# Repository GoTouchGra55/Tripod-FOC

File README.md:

# Tripod (FOC)

A device that works as the brushless FOC motor driver of a tri-legged hopping robot!

## Overview

Tripod-FOC is a 4 layer printed circuit board which is to be used as the field-oriented control based motor driver of a major robot project I've been working on.

The board handles the robot's main motor control providing the necessary measurement for its brushless motors.

## Design

### Routes

### Schematics

SEE [SCHEMATICS](KiCAD/FOC.pdf)

## Build Instructions

1. Order the PCB using the provided [files](KiCAD/production).
2. Solder all SMD components according to the schematic and PCB layout.
3. Inspect all solder joints and check for shorts.
4. Connect the peripherals according to the schematic.
5. Flash the firmware and verify all interfaces.
6. Test the power rails before connecting the motors.

## BOM

| Category           | Item             |    Quantity | Supplier     | Unit Cost (USD) | Total Cost (USD) | Notes                               |
| ------------------ | ---------------- | ----------: | ------------ | --------------: | ---------------: | ----------------------------------- |
| PCB manufacturing  | JLCPCB order     |           1 | JLCPCB       |         $427.16 |          $427.16 | JLCPCB order subtotal               |
| Shipping           | FedEx shipping   |           1 | FedEx        |          $36.62 |           $36.62 | Included in the quoted JLCPCB total |
| Passive components | SMD resistors    | As required | Daraz        |           $0.00 |            $0.00 | Already owned                       |
| Passive components | SMD capacitors   | As required | Daraz        |           $0.00 |            $0.00 | Already owned                       |
| Passive components | Circular magnets |      1 pack | Amazon India |           $2.65 |            $2.65 | Ordered from amazon.in              |
| **TOTAL**          |                  |             |              |                 |      **$466.43** |                                     |

### SEE [BOM](BOM.csv)

## IMPORTANT

1. Use a 3-4s LiPo battery if you decide to use this board in your project. Discard the battery if it smells "funny".

2. Check for any damage on the pcb as it can be the reason for a catastrophic failure.

## License

MIT-License - SEE [LICENSE](LICENSE)

## Author

Shaurya Tamang  
Contact: [Email](shauryatamand.dev@gmail.com)

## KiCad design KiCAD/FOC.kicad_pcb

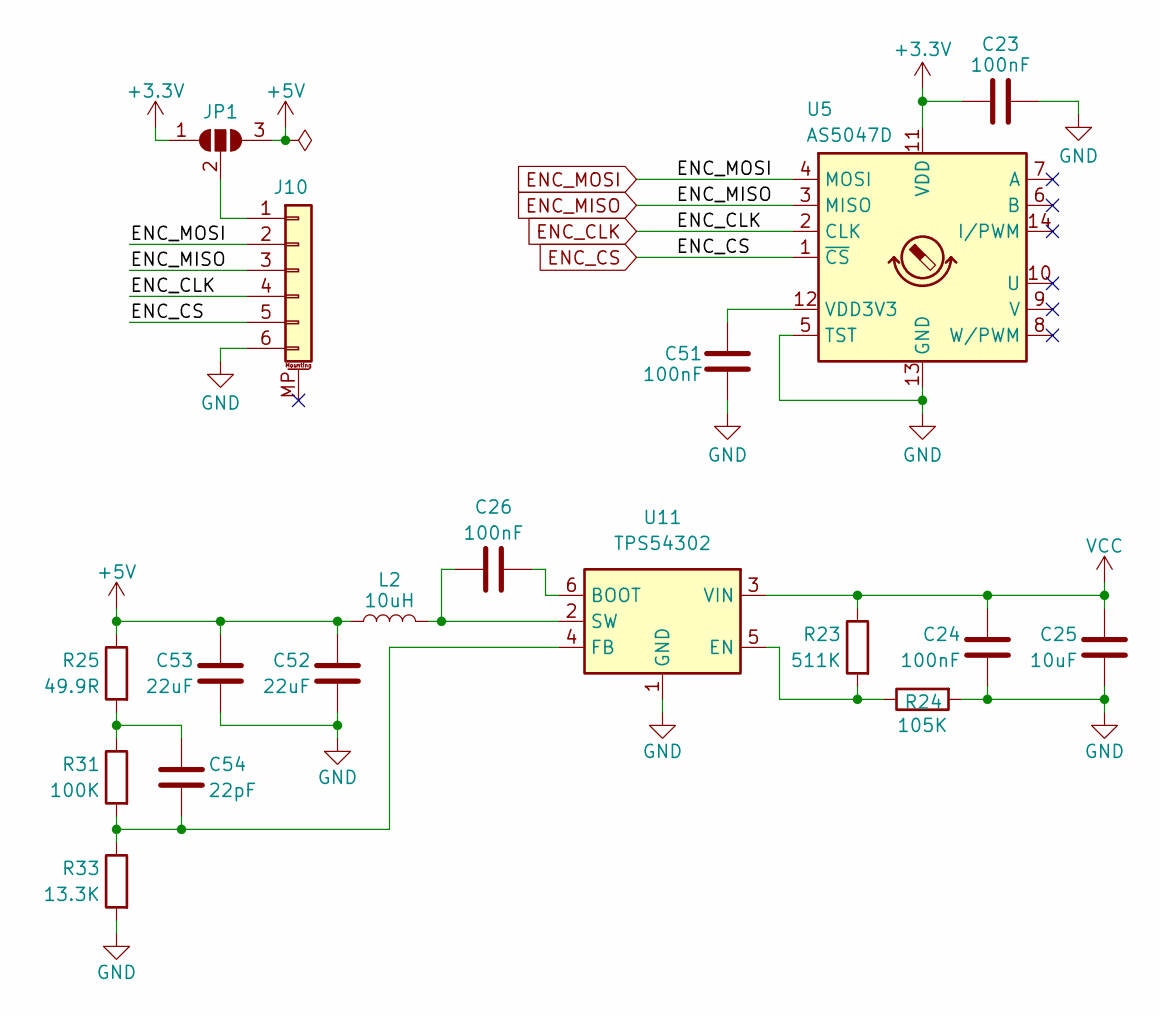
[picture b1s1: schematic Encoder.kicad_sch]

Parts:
C23, C24, C26, C51: 100nF; C_0402_1005Metric
C25: 10uF; C_0603_1608Metric
C52, C53: 22uF; C_0603_1608Metric
C54: 22pF; C_0402_1005Metric
J10: Conn_01x06_MountingPin; JST_SH_SM06B-SRSS-TB_1x06-1MP_P1.00mm_Horizontal
JP1: SolderJumper_3_Open; SolderJumper-3_P1.3mm_Open_Pad1.0x1.5mm_NumberLabels
L2: 10uH; L_Cenker_CKCS3012
R23: 511K; R_0603_1608Metric
R24: 105K; R_0603_1608Metric
R25: 49.9R; R_0402_1005Metric
R31: 100K; R_0603_1608Metric
R33: 13.3K; R_0603_1608Metric
U5: AS5047D; TSSOP-14_4.4x5mm_P0.65mm
U11: TPS54302; SOT-23-6

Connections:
+3.3V: C23.1, JP1.1 (A), U5.11 (VDD); also elsewhere on the board
+5V: C52.1, C53.1, JP1.3 (B), L2.2, R25.1; also elsewhere on the board
ENC_CLK: J10.4, U5.2 (CLK); also elsewhere on the board
ENC_CS: J10.5, U5.1 (~CS); also elsewhere on the board
ENC_MISO: J10.3, U5.3 (MISO); also elsewhere on the board
ENC_MOSI: J10.2, U5.4 (MOSI); also elsewhere on the board
GND: C23.2, C24.2, C25.2, C51.1, C52.2, C53.2, J10.6, R24.2, R33.2, U5.5 (TST), U5.13 (GND), U11.1 (GND); also elsewhere on the board
unnamed: C54.1, R25.2, R31.1
unnamed: J10.1, JP1.2 (C)
unnamed: C51.2, U5.12 (VDD3V3)
unnamed: C26.1, U11.6 (BOOT)
unnamed: R23.2, R24.1, U11.5 (EN)
unnamed: C54.2, R31.2, R33.1, U11.4 (FB)
unnamed: C26.2, L2.1, U11.2 (SW)
VCC: C24.1, C25.1, R23.1, U11.3 (VIN); also elsewhere on the board

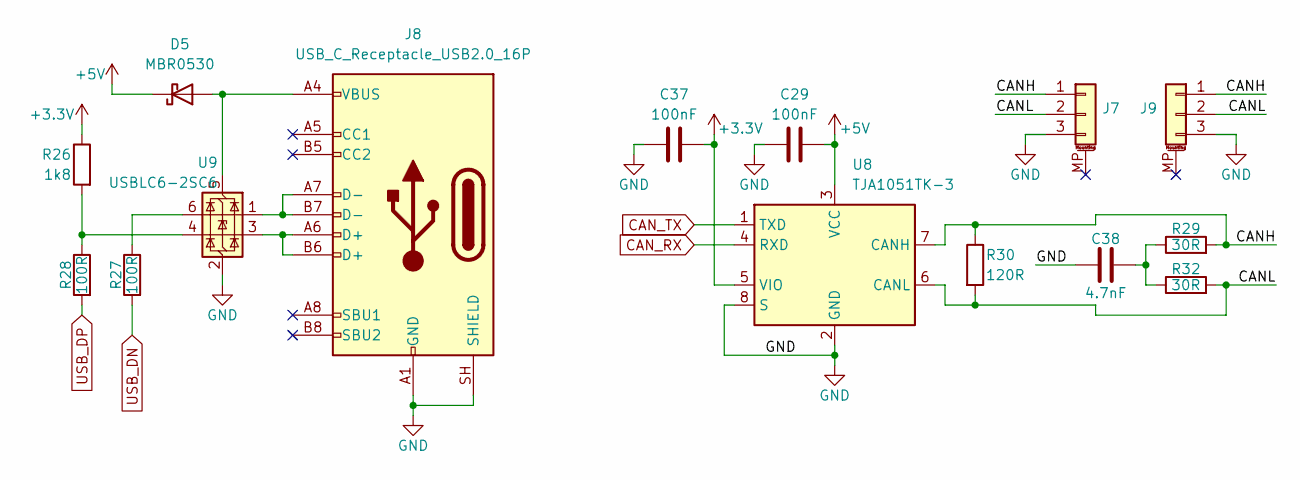
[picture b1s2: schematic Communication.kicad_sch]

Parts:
C29, C37: 100nF; C_0402_1005Metric
C38: 4.7nF; C_0402_1005Metric
D5: MBR0530; D_SOD-123; LCSC Part # C5204746
J7, J9: Conn_01x03_MountingPin; JST_SH_SM03B-SRSS-TB_1x03-1MP_P1.00mm_Horizontal
J8: USB_C_Receptacle_USB2.0_16P; USB_C_Receptacle_GCT_USB4105-xx-A_16P_TopMnt_Horizontal
R26: 1k8; R_0402_1005Metric; LCSC Part # C163481
R27, R28: 100R; R_0402_1005Metric; LCSC Part # C705627
R29, R32: 30R; R_0402_1005Metric; LCSC Part # C852718
R30: 120R; R_0402_1005Metric; LCSC Part # C125925
U8: TJA1051TK-3; HVSON-8-1EP_3x3mm_P0.65mm_EP1.6x2.4mm
U9: USBLC6-2SC6; SOT-23-6; LCSC Part # C2827654

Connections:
+3.3V: C37.2, R26.1, U8.5 (VIO); also elsewhere on the board
+5V: C29.2, D5.1 (K), U8.3 (VCC); also elsewhere on the board
/Communication/CANH: J7.1, J9.1, R29.2, R30.1, U8.7 (CANH)
/Communication/CANL: J7.2, J9.2, R30.2, R32.2, U8.6 (CANL)
CAN_RX: U8.4 (RXD); also elsewhere on the board
CAN_TX: U8.1 (TXD); also elsewhere on the board
GND: C29.1, C37.1, C38.1, J7.3, J8.A1 (GND), J8.A12 (GND), J8.B1 (GND), J8.B12 (GND), J8.SH (SHIELD), J9.3, U8.2 (GND), U8.8 (S), U8.9 (GND), U9.2 (GND); also elsewhere on the board
unnamed: C38.2, R29.1, R32.1
unnamed: D5.2 (A), J8.A4 (VBUS), J8.A9 (VBUS), J8.B4 (VBUS), J8.B9 (VBUS), U9.5 (VBUS)
unnamed: J8.A6 (D+), J8.B6 (D+), U9.3 (I/O2)
unnamed: J8.A7 (D-), J8.B7 (D-), U9.1 (I/O1)
unnamed: R26.2, R28.1, U9.4 (I/O2)
unnamed: R27.1, U9.6 (I/O1)
USB_DN: R27.2; also elsewhere on the board
USB_DP: R28.2; also elsewhere on the board

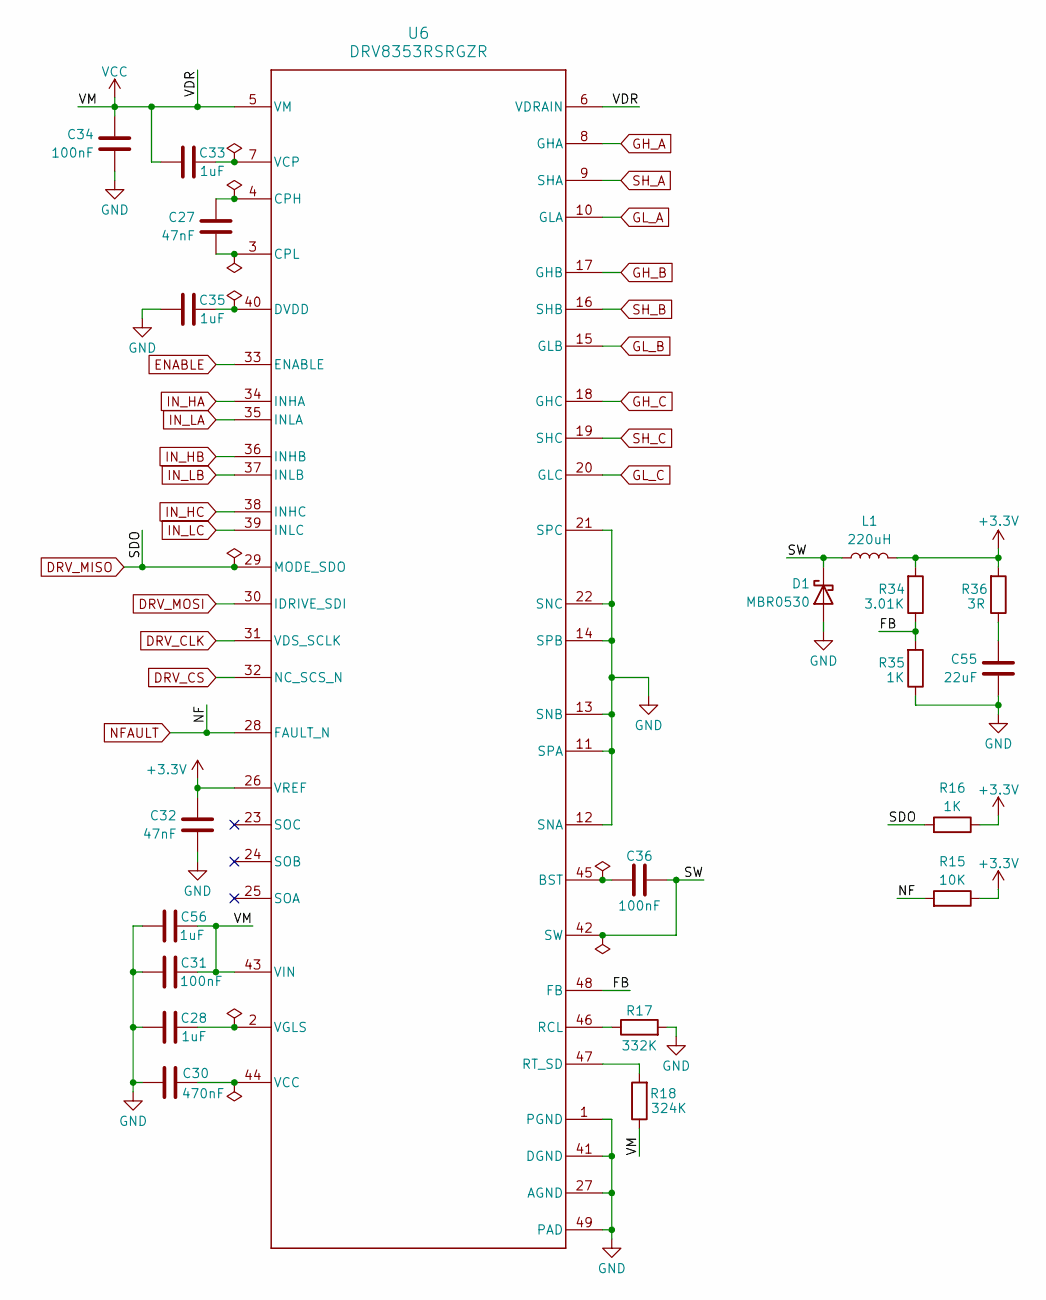
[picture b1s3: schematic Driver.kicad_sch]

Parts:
C27, C32: 47nF; C_0402_1005Metric
C28, C33, C35, C56: 1uF; C_0603_1608Metric
C30: 470nF; C_0402_1005Metric
C31, C34, C36: 100nF; C_0402_1005Metric
C55: 22uF; C_0603_1608Metric
D1: MBR0530; R_0402_1005Metric
L1: 220uH; L_Cenker_CKCS5040
R15: 10K; R_0603_1608Metric
R16, R35: 1K; R_0402_1005Metric
R17: 332K; R_0603_1608Metric
R18: 324K; R_0603_1608Metric
R34: 3.01K; R_0603_1608Metric
R36: 3R; R_0402_1005Metric
U6: DRV8353RSRGZR; RGZ0048L

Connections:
+3.3V: C32.1, L1.1, R15.1, R16.1, R34.2, R36.2, U6.26 (VREF); also elsewhere on the board
/Driver/FB: R34.1, R35.2, U6.48 (FB)
/Driver/SW: C36.1, D1.1 (K), L1.2, U6.42 (SW)
DRV_CLK: U6.31 (VDS_SCLK); also elsewhere on the board
DRV_CS: U6.32 (NC_SCS_N); also elsewhere on the board
DRV_MISO: R16.2, U6.29 (MODE_SDO); also elsewhere on the board
DRV_MOSI: U6.30 (IDRIVE_SDI); also elsewhere on the board
ENABLE: U6.33 (ENABLE); also elsewhere on the board
GH_A: U6.8 (GHA); also elsewhere on the board
GH_B: U6.17 (GHB); also elsewhere on the board
GH_C: U6.18 (GHC); also elsewhere on the board
GL_A: U6.10 (GLA); also elsewhere on the board
GL_B: U6.15 (GLB); also elsewhere on the board
GL_C: U6.20 (GLC); also elsewhere on the board
GND: C28.1, C30.1, C31.1, C32.2, C34.2, C35.1, C55.2, C56.1, D1.2 (A), R17.2, R35.1, U6.1 (PGND), U6.11 (SPA), U6.12 (SNA), U6.13 (SNB), U6.14 (SPB), U6.21 (SPC), U6.22 (SNC), U6.27 (AGND), U6.41 (DGND), U6.49 (PAD); also elsewhere on the board
IN_HA: U6.34 (INHA); also elsewhere on the board
IN_HB: U6.36 (INHB); also elsewhere on the board
IN_HC: U6.38 (INHC); also elsewhere on the board
IN_LA: U6.35 (INLA); also elsewhere on the board
IN_LB: U6.37 (INLB); also elsewhere on the board
IN_LC: U6.39 (INLC); also elsewhere on the board
NFAULT: R15.2, U6.28 (FAULT_N); also elsewhere on the board
unnamed: C55.1, R36.1
unnamed: C36.2, U6.45 (BST)
unnamed: C27.1, U6.4 (CPH)
unnamed: C27.2, U6.3 (CPL)
unnamed: C35.2, U6.40 (DVDD)
unnamed: R17.1, U6.46 (RCL)
unnamed: R18.2, U6.47 (RT_SD)
unnamed: C30.2, U6.44 (VCC)
unnamed: C33.2, U6.7 (VCP)
unnamed: C28.2, U6.2 (VGLS)
SH_A: U6.9 (SHA); also elsewhere on the board
SH_B: U6.16 (SHB); also elsewhere on the board
SH_C: U6.19 (SHC); also elsewhere on the board
VCC: C31.2, C33.1, C34.1, C56.2, R18.1, U6.5 (VM), U6.6 (VDRAIN), U6.43 (VIN); also elsewhere on the board

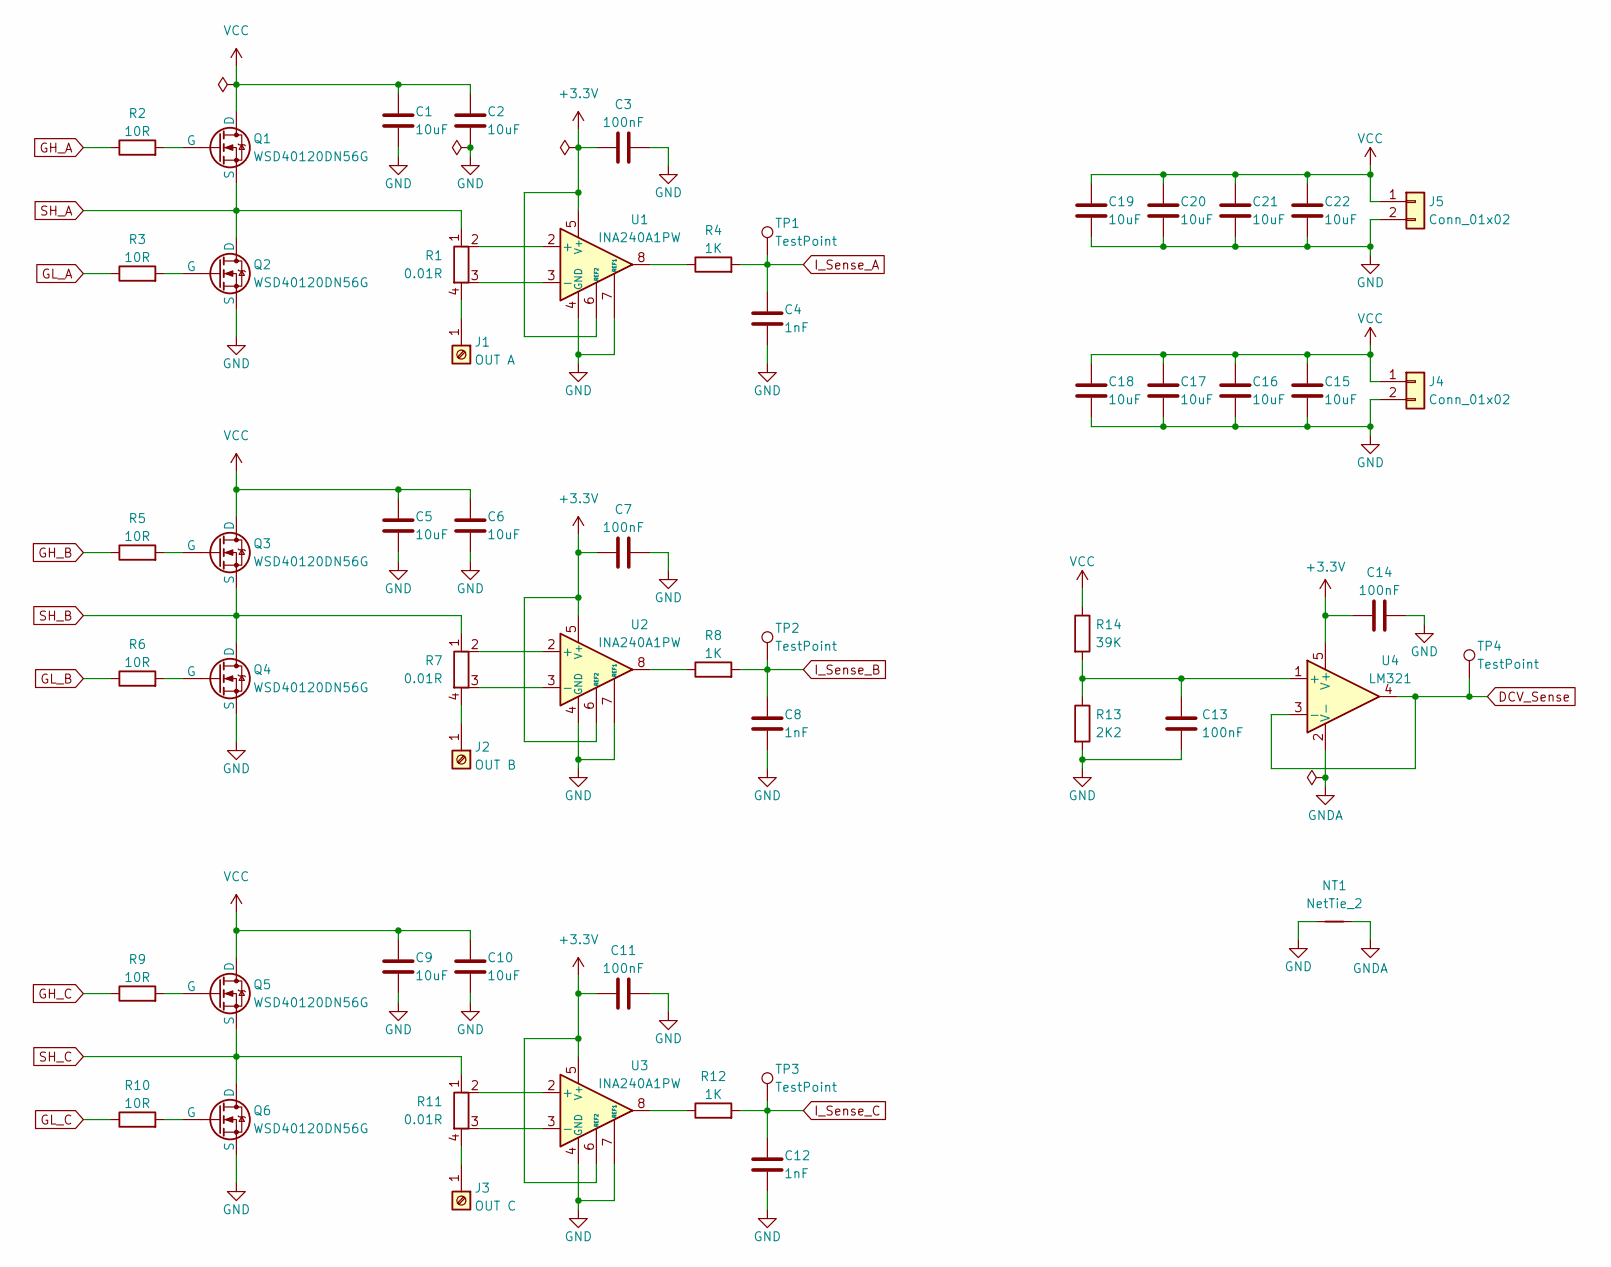
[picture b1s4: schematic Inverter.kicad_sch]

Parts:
C1, C2, C5, C6, C9, C10, C15, C16, C17, C18, C19, C20, C21, C22: 10uF; C_0603_1608Metric
C3, C7, C11, C13, C14: 100nF; C_0402_1005Metric
C4, C8, C12: 1nF; C_0402_1005Metric
J1: OUT A; CONN_01x01
J2: OUT B; CONN_01x01
J3: OUT C; CONN_01x01
J4, J5: Conn_01x02; AMASS_XT30PW-M_1x02_P2.50mm_Horizontal
NT1: NetTie_2; NetTie-2_SMD_Pad0.5mm
Q1, Q2, Q3, Q4, Q5, Q6: WSD40120DN56G; AO_DFN-8-1EP_5.55x5.2mm_P1.27mm_EP4.12x4.6mm
R1, R7, R11: 0.01R; R_Shunt_Vishay_WSK2512_6332Metric_T1.19mm
R2, R3, R5, R6, R9, R10: 10R; R_0402_1005Metric
R4, R8, R12: 1K; R_0402_1005Metric
R13: 2K2; R_0603_1608Metric
R14: 39K; R_0805_2012Metric
TP1, TP2, TP3, TP4: TestPoint; TestPoint_Pad_D1.5mm
U1, U2, U3: INA240A1PW; TSSOP-8_4.4x3mm_P0.65mm
U4: LM321; SOT-23-5

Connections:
+3.3V: C3.1, C7.1, C11.1, C14.1, U1.5 (V+), U1.6 (REF2), U2.5 (V+), U2.6 (REF2), U3.5 (V+), U3.6 (REF2), U4.5 (V+); also elsewhere on the board
DCV_Sense: TP4.1 (1_1), U4.3 (-), U4.4; also elsewhere on the board
GH_A: R2.1; also elsewhere on the board
GH_B: R5.1; also elsewhere on the board
GH_C: R9.1; also elsewhere on the board
GL_A: R3.1; also elsewhere on the board
GL_B: R6.1; also elsewhere on the board
GL_C: R10.1; also elsewhere on the board
GND: C1.2, C2.2, C3.2, C4.2, C5.2, C6.2, C7.2, C8.2, C9.2, C10.2, C11.2, C12.2, C13.2, C14.2, C15.2, C16.2, C17.2, C18.2, C19.2, C20.2, C21.2, C22.2, J4.2, J5.2, NT1.1, Q2.3 (S), Q4.3 (S), Q6.3 (S), R13.2, U1.1 (GND), U1.4 (GND), U1.7 (REF1), U2.1 (GND), U2.4 (GND), U2.7 (REF1), U3.1 (GND), U3.4 (GND), U3.7 (REF1); also elsewhere on the board
GNDA: NT1.2, U4.2 (V-)
I_Sense_A: C4.1, R4.2, TP1.1 (1_1); also elsewhere on the board
I_Sense_B: C8.1, R8.2, TP2.1 (1_1); also elsewhere on the board
I_Sense_C: C12.1, R12.2, TP3.1 (1_1); also elsewhere on the board
unnamed: J1.1 (Pin_1_1), R1.4
unnamed: J2.1 (Pin_1_1), R7.4
unnamed: J3.1 (Pin_1_1), R11.4
unnamed: Q1.2 (G), R2.2
unnamed: Q2.2 (G), R3.2
unnamed: Q3.2 (G), R5.2
unnamed: Q4.2 (G), R6.2
unnamed: Q5.2 (G), R9.2
unnamed: Q6.2 (G), R10.2
unnamed: R4.1, U1.8
unnamed: R8.1, U2.8
unnamed: R12.1, U3.8
unnamed: R1.2, U1.2 (+)
unnamed: R1.3, U1.3 (-)
unnamed: R7.2, U2.2 (+)
unnamed: R7.3, U2.3 (-)
unnamed: R11.2, U3.2 (+)
unnamed: R11.3, U3.3 (-)
unnamed: C13.1, R13.1, R14.2, U4.1 (+)
SH_A: Q1.3 (S), Q2.1 (D), R1.1; also elsewhere on the board
SH_B: Q3.3 (S), Q4.1 (D), R7.1; also elsewhere on the board
SH_C: Q5.3 (S), Q6.1 (D), R11.1; also elsewhere on the board
VCC: C1.1, C2.1, C5.1, C6.1, C9.1, C10.1, C15.1, C16.1, C17.1, C18.1, C19.1, C20.1, C21.1, C22.1, J4.1, J5.1, Q1.1 (D), Q3.1 (D), Q5.1 (D), R14.1; also elsewhere on the board

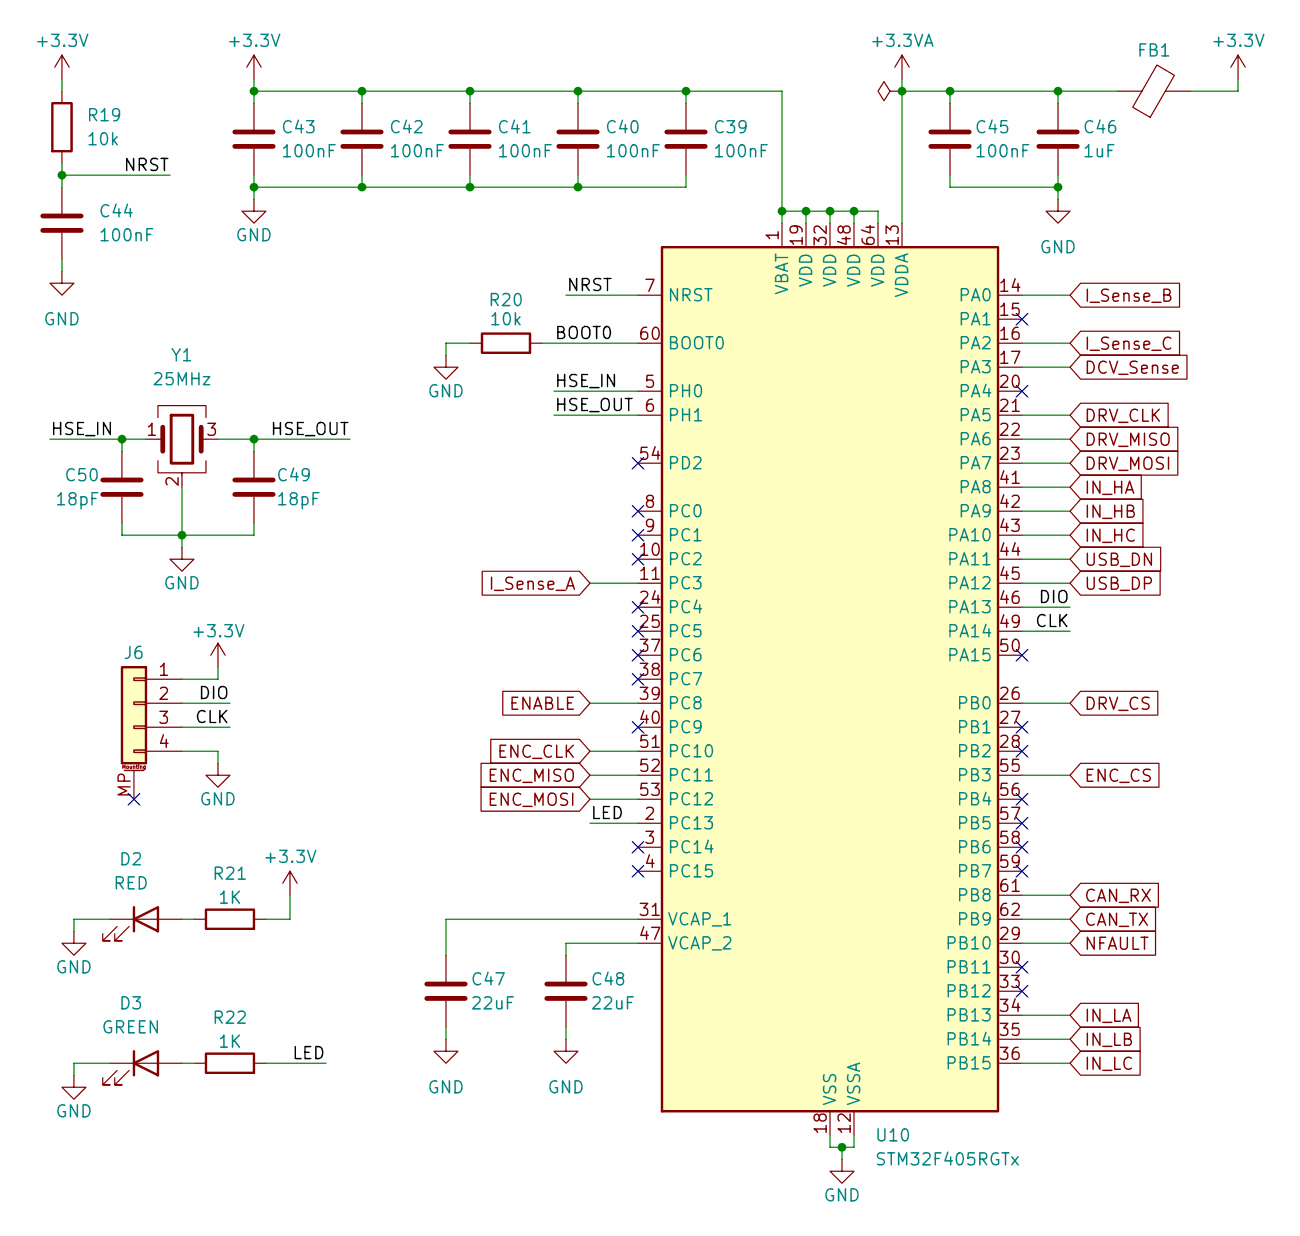
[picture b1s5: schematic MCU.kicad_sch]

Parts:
C39, C40, C41, C42, C43: 100nF; C_0402_1005Metric
C44, C45: 100nF; C_0402_1005Metric; LCSC Part # C1525
C46: 1uF; C_0603_1608Metric; LCSC Part # C29266
C47, C48: 22uF; C_0603_1608Metric; LCSC Part # C1525
C49, C50: 18pF; C_0402_1005Metric
D2: RED; LED_0402_1005Metric
D3: GREEN; LED_0402_1005Metric
FB1: fcm 1608-0603; D_0603_1608Metric; LCSC Part # C19330
J6: Conn_01x04_MountingPin; JST_SH_SM04B-SRSS-TB_1x04-1MP_P1.00mm_Horizontal
R19, R20: 10k; R_0603_1608Metric; LCSC Part # C60490
R21, R22: 1K; R_0402_1005Metric
U10: STM32F405RGTx; LQFP-64_10x10mm_P0.5mm
Y1: 25MHz; Crystal_SMD_3225-4Pin_3.2x2.5mm

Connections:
+3.3V: C39.1, C40.1, C41.1, C42.1, C43.1, FB1.2, J6.1, R19.1, R21.2, U10.1 (VBAT), U10.19 (VDD), U10.32 (VDD), U10.48 (VDD), U10.64 (VDD); also elsewhere on the board
+3.3VA: C45.1, C46.1, FB1.1, U10.13 (VDDA)
/MCU/BOOT0: R20.2, U10.60 (BOOT0)
/MCU/CLK: J6.3, U10.49 (PA14)
/MCU/DIO: J6.2, U10.46 (PA13)
/MCU/HSE_IN: C50.1, U10.5 (PH0), Y1.1
/MCU/HSE_OUT: C49.1, U10.6 (PH1), Y1.3
/MCU/LED: R22.2, U10.2 (PC13)
/MCU/NRST: C44.1, R19.2, U10.7 (NRST)
CAN_RX: U10.61 (PB8); also elsewhere on the board
CAN_TX: U10.62 (PB9); also elsewhere on the board
DCV_Sense: U10.17 (PA3); also elsewhere on the board
DRV_CLK: U10.21 (PA5); also elsewhere on the board
DRV_CS: U10.26 (PB0); also elsewhere on the board
DRV_MISO: U10.22 (PA6); also elsewhere on the board
DRV_MOSI: U10.23 (PA7); also elsewhere on the board
ENABLE: U10.39 (PC8); also elsewhere on the board
ENC_CLK: U10.51 (PC10); also elsewhere on the board
ENC_CS: U10.55 (PB3); also elsewhere on the board
ENC_MISO: U10.52 (PC11); also elsewhere on the board
ENC_MOSI: U10.53 (PC12); also elsewhere on the board
GND: C39.2, C40.2, C41.2, C42.2, C43.2, C44.2, C45.2, C46.2, C47.2, C48.2, C49.2, C50.2, D2.1 (K), D3.1 (K), J6.4, R20.1, U10.12 (VSSA), U10.18 (VSS), U10.63 (VSS), Y1.2 (G), Y1.4 (G); also elsewhere on the board
IN_HA: U10.41 (PA8); also elsewhere on the board
IN_HB: U10.42 (PA9); also elsewhere on the board
IN_HC: U10.43 (PA10); also elsewhere on the board
IN_LA: U10.34 (PB13); also elsewhere on the board
IN_LB: U10.35 (PB14); also elsewhere on the board
IN_LC: U10.36 (PB15); also elsewhere on the board
I_Sense_A: U10.11 (PC3); also elsewhere on the board
I_Sense_B: U10.14 (PA0); also elsewhere on the board
I_Sense_C: U10.16 (PA2); also elsewhere on the board
NFAULT: U10.29 (PB10); also elsewhere on the board
unnamed: D2.2 (A), R21.1
unnamed: D3.2 (A), R22.1
unnamed: C47.1, U10.31 (VCAP_1)
unnamed: C48.1, U10.47 (VCAP_2)
USB_DN: U10.44 (PA11); also elsewhere on the board
USB_DP: U10.45 (PA12); also elsewhere on the board

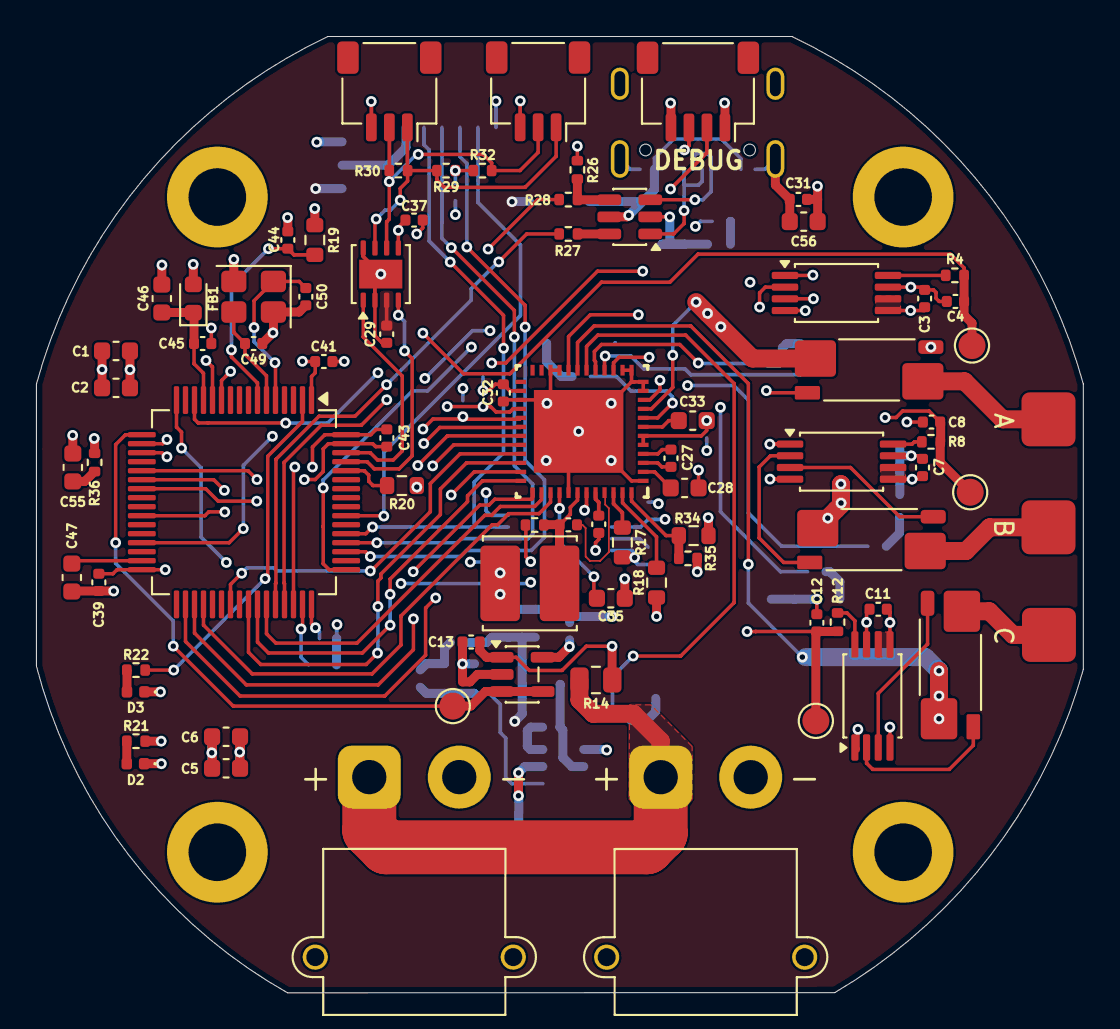
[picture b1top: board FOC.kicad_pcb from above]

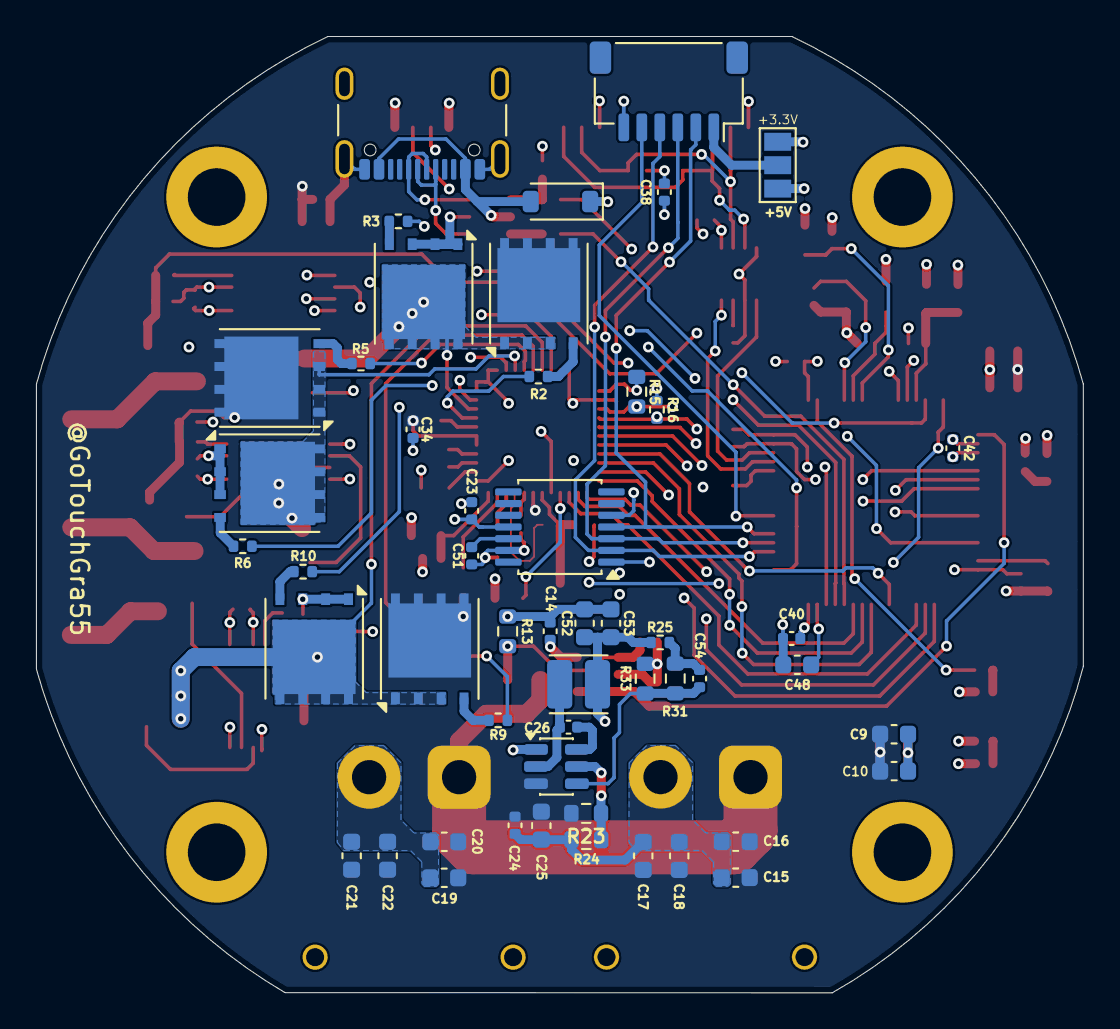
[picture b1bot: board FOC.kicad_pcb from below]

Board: 4 copper layers, 58.2 x 53.1 mm, 132 parts (51 on the bottom side), 96 nets.

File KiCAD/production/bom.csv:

Designator,Footprint,Quantity,Value,LCSC Part #
"C1, C10, C15, C16, C17, C18, C19, C2, C20, C21, C22, C25, C5, C6, C9",0603,15,10uF,
"C11, C13, C14, C23, C24, C26, C29, C3, C31, C34, C36, C37, C39, C40, C41, C42, C43, C51, C7",0402,19,100nF,
"C12, C4, C8",0402,3,1nF,
"C27, C32",0402,2,47nF,
"C28, C33, C35, C56",0603,4,1uF,
C30,0402,1,470nF,
C38,0402,1,4.7nF,
"C44, C45",0402,2,100nF,C1525
C46,0603,1,1uF,C29266
"C47, C48",0603,2,22uF,C1525
"C49, C50",0402,2,18pF,
"C52, C53, C55",0603,3,22uF,
C54,0402,1,22pF,
D1,D_SOD-123,1,MBR0530,
D2,0402,1,RED,
D3,0402,1,GREEN,
D5,D_SOD-123,1,MBR0530,C5204746
FB1,0603,1,fcm 1608-0603,C19330
J1,CONN_01x01,1,OUT A,
J10,JST_SH_SM06B-SRSS-TB_1x06-1MP_P1.00mm_Horizontal,1,Conn_01x06_MountingPin,
J2,CONN_01x01,1,OUT B,
J3,CONN_01x01,1,OUT C,
"J4, J5",AMASS_XT30PW-M_1x02_P2.50mm_Horizontal,2,Conn_01x02,
J6,JST_SH_SM04B-SRSS-TB_1x04-1MP_P1.00mm_Horizontal,1,Conn_01x04_MountingPin,
"J7, J9",JST_SH_SM03B-SRSS-TB_1x03-1MP_P1.00mm_Horizontal,2,Conn_01x03_MountingPin,
J8,USB_C_Receptacle_GCT_USB4105-xx-A_16P_TopMnt_Horizontal,1,USB_C_Receptacle_USB2.0_16P,
L1,L_Cenker_CKCS5040,1,220uH,
L2,L_Cenker_CKCS3012,1,10uH,
"Q1, Q2, Q3, Q4, Q5, Q6",AO_DFN-8-1EP_5.55x5.2mm_P1.27mm_EP4.12x4.6mm,6,WSD40120DN56G,
"R1, R11, R7",R_Shunt_Vishay_WSK2512_6332Metric_T1.19mm,3,0.01R,
"R10, R2, R3, R5, R6, R9",0402,6,10R,
"R12, R16, R21, R22, R35, R4, R8",0402,7,1K,
R13,0603,1,2K2,
R14,0805,1,39K,
R15,0603,1,10K,
R17,0603,1,332K,
R18,0603,1,324K,
"R19, R20",0603,2,10k,C60490
R23,0603,1,511K,
R24,0603,1,105K,
R25,0402,1,49.9R,
R26,0402,1,1k8,C163481
"R27, R28",0402,2,100R,C705627
"R29, R32",0402,2,30R,C852718
R30,0402,1,120R,C125925
R31,0603,1,100K,
R33,0603,1,13.3K,
R34,0603,1,3.01K,
R36,0402,1,3R,
"TP1, TP2, TP3, TP4",TestPoint_Pad_D1.5mm,4,TestPoint,
"U1, U2, U3",TSSOP-8_4.4x3mm_P0.65mm,3,INA240A1PW,
U10,LQFP-64_10x10mm_P0.5mm,1,STM32F405RGTx,
U11,SOT-23-6,1,TPS54302,
U4,SOT-23-5,1,LM321,
U5,TSSOP-14_4.4x5mm_P0.65mm,1,AS5047D,
U6,RGZ0048L,1,DRV8353RSRGZR,
U8,HVSON-8-1EP_3x3mm_P0.65mm_EP1.6x2.4mm,1,TJA1051TK-3,
U9,SOT-23-6,1,USBLC6-2SC6,C2827654
Y1,Crystal_SMD_3225-4Pin_3.2x2.5mm,1,25MHz,

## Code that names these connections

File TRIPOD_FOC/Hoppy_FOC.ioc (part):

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Mcu.Name=STM32F405RGTx
Mcu.Package=LQFP64
Mcu.UserName=STM32F405RGTx
PA0-WKUP.GPIOParameters=GPIO_Label
PA0-WKUP.GPIO_Label=I_SENSE_B
PA0-WKUP.Signal=ADCx_IN0
PA10.GPIOParameters=GPIO_Label
PA10.GPIO_Label=IN_HC
PA10.Signal=S_TIM1_CH3
PA11.Mode=Host_Only
PA11.Signal=USB_OTG_FS_DM
PA12.Mode=Host_Only
PA12.Signal=USB_OTG_FS_DP
PA13.Mode=Serial_Wire
PA13.Signal=SYS_JTMS-SWDIO
PA14.Mode=Serial_Wire
PA14.Signal=SYS_JTCK-SWCLK
PA2.GPIOParameters=GPIO_Label
PA2.GPIO_Label=I_SENSE_C
PA2.Signal=ADCx_IN2
PA3.GPIOParameters=GPIO_Label
PA3.GPIO_Label=DCV_SENSE
PA3.Signal=ADCx_IN3
PA5.GPIOParameters=GPIO_Label
PA5.GPIO_Label=DRV_SCK
PA5.Mode=Full_Duplex_Master
PA5.Signal=SPI1_SCK
PA6.GPIOParameters=GPIO_Label
PA6.GPIO_Label=DRV_MISO
PA6.Mode=Full_Duplex_Master
PA6.Signal=SPI1_MISO
PA7.GPIOParameters=GPIO_Label
PA7.GPIO_Label=DRV_MOSI
PA7.Mode=Full_Duplex_Master
PA7.Signal=SPI1_MOSI
PA8.GPIOParameters=GPIO_Label
PA8.GPIO_Label=IN_HA
PA8.Signal=S_TIM1_CH1
PA9.GPIOParameters=GPIO_Label
PA9.GPIO_Label=IN_HB
PA9.Signal=S_TIM1_CH2
PB0.GPIOParameters=GPIO_Label
PB0.GPIO_Label=DRV_CS
PB0.Signal=GPIO_Output
PB10.GPIOParameters=GPIO_Label
PB10.GPIO_Label=NFAULT
PB10.Signal=GPIO_Output
PB13.GPIOParameters=GPIO_Label
PB13.GPIO_Label=IN_LA
PB13.Signal=TIM1_CH1N
PB14.GPIOParameters=GPIO_Label
PB14.GPIO_Label=IN_LB
PB14.Signal=TIM1_CH2N
PB15.GPIOParameters=GPIO_Label
PB15.GPIO_Label=IN_LC
PB15.Signal=TIM1_CH3N
PB3.GPIOParameters=GPIO_Label
PB3.GPIO_Label=ENC__CS
PB3.Signal=GPIO_Output
PB8.Mode=CAN_Activate
PB8.Signal=CAN1_RX
PB9.Mode=CAN_Activate
PB9.Signal=CAN1_TX
PC10.GPIOParameters=GPIO_Label
PC10.GPIO_Label=ENC_SCK
PC10.Mode=Full_Duplex_Master
PC10.Signal=SPI3_SCK
PC11.GPIOParameters=GPIO_Label
PC11.GPIO_Label=ENC_MISO
PC11.Mode=Full_Duplex_Master
PC11.Signal=SPI3_MISO
PC12.GPIOParameters=GPIO_Label
PC12.GPIO_Label=ENC_MOSI
PC12.Mode=Full_Duplex_Master
PC12.Signal=SPI3_MOSI
PC3.GPIOParameters=GPIO_Label
PC3.GPIO_Label=I_SENSE_A
PC3.Signal=ADCx_IN13
PC8.GPIOParameters=GPIO_Label
PC8.GPIO_Label=ENABLE
PC8.Signal=GPIO_Output
PH0-OSC_IN.Mode=HSE-External-Oscillator
PH0-OSC_IN.Signal=RCC_OSC_IN
PH1-OSC_OUT.Mode=HSE-External-Oscillator
PH1-OSC_OUT.Signal=RCC_OSC_OUT
RCC.HSE_VALUE=25000000
RCC.SYSCLKFreq_VALUE=168000000
RCC.SYSCLKSource=RCC_SYSCLKSOURCE_PLLCLK
board=custom
